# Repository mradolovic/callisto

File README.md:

# callisto
Official repository of the Visnjan Observatory e-Callisto station

Members of the Visnjan Callisto group:<br>
<br>
Marko Radolović<br>
Matej Marković<br>
Danko Marušić<br>
Korado Korlević<br>

[e-callisto.org](https://e-callisto.org/)

We owe a big thank you for helping, in this or that way, to the following:

Christian Monstein, Istituto ricerche solari Aldo e Cele Daccò<br>
Alessandro Marassi, Osservatiorio Astronomico di Trieste<br>
Mario Cifrek, Faculty of Electrical Engineering and Computing Zagreb<br>
Silvio Hrabar, Faculty of Electrical Engineering and Computing Zagreb<br>
Darin Nožina, Faculty of Electrical Engineering and Computing Zagreb<br>
Adam Alićajić, 9A4QV<br>

The CALLISTO spectrometer is a programmable heterodyne receiver designed 2006 in the framework of IHY2007 and ISWI by Christian Monstein (PI) as member of the former Radio Astronomy Group (RAG) at ETH Zurich, Switzerland. CALLISTO is an artificial word, composed as 'Compound Astronomical Low frequency Low cost Instrument for Spectroscopy and Transportable Observatory'. The main applications are observation of solar radio bursts for astronomical science, education, outreach and citizen science as well as rfi-monitoring. The instrument natively operates between 45 and 870 MHz using a modern, commercially available broadband cable-TV tuner CD1316 having a frequency resolution of 62.5 KHz. 

The data obtained from CALLISTO are FIT-files with up to 400 frequencies per sweep. The data are transferred via a RS-232 cable to a computer and saved locally. Time resolution is 0.25 sec at 200 channels per spectrum (800 spectral pixels per second). The integration time is 1 msec and the radiometric bandwidth is about 300 KHz. The overall dynamic range is larger than 50 dB. For convenient data handling several IDL-, PERL- and Python-routines were written.

Many CALLISTO instruments have already been deployed worldwide through the IHY/UNBSSI and ISWI instrument deployment program, CALLISTO is able to continuously observe the solar radio spectrum for 24h per day through all the year. All CALLISTO spectrometers together form the e-Callisto network. CALLISTO in addition is dedicated to perform radio-monitoring within its frequency range with 13'200 channels per spectrum. The frequency range can be expanded to any range by switching-in a heterodyne up- or a down-converter. Data from individual instruments are automatically uploaded by FTP to the central server at FHNW. Data which are not locked to UTC (either from the past or from the future) generate an error report.

Instrument deployment including education and training of observers was financially supported by SNF, SSAA, NASA, Institute for Astronomy and ETH Global, formerly known as North-South Center of ETH Zurich and a few private sponsors.

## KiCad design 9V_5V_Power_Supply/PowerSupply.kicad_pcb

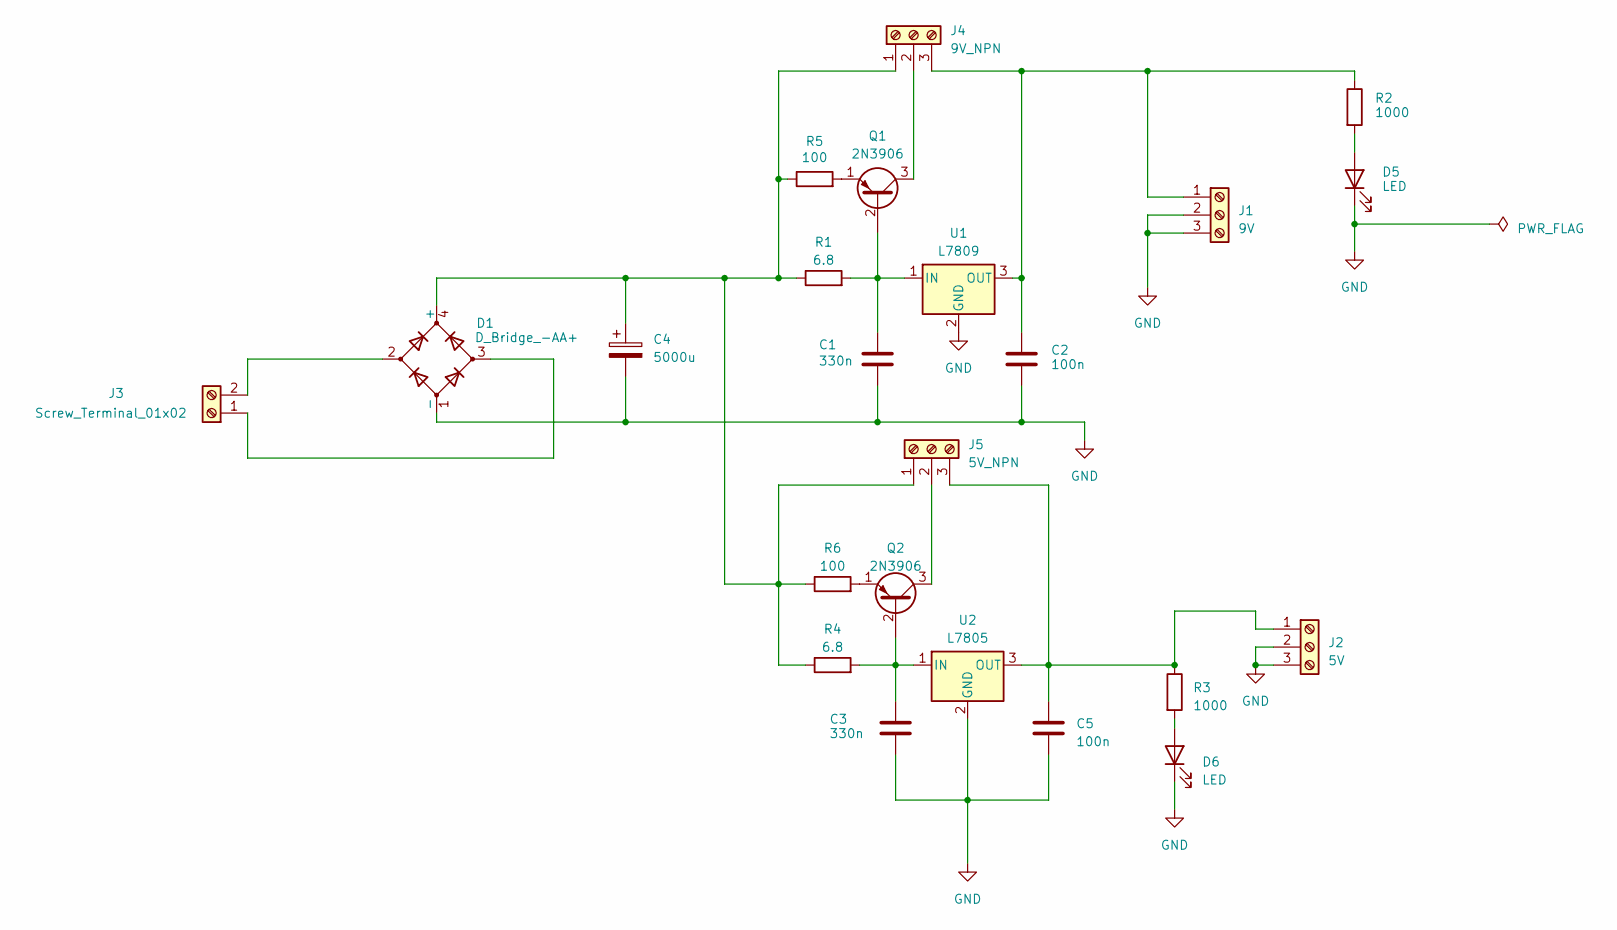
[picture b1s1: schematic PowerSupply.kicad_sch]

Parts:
C1, C3: 330n; C_Disc_D5.0mm_W2.5mm_P5.00mm
C2, C5: 100n; C_Disc_D5.0mm_W2.5mm_P5.00mm
C4: 5000u; CP_Radial_D10.0mm_P5.00mm
D1: D_Bridge_-AA+; PBL405
D5, D6: LED; LED_D3.0mm
J1: 9V; TerminalBlock_bornier-3_P5.08mm
J2: 5V; TerminalBlock_bornier-3_P5.08mm
J3: Screw_Terminal_01x02; TerminalBlock_bornier-2_P5.08mm
J4: 9V_NPN; TerminalBlock_bornier-3_P5.08mm
J5: 5V_NPN; TerminalBlock_bornier-3_P5.08mm
Q1, Q2: 2N3906; TO-92_Inline_Wide
R1, R4: 6.8; R_Axial_DIN0516_L15.5mm_D5.0mm_P20.32mm_Horizontal
R2, R3: 1000; R_0805_2012Metric_Pad1.20x1.40mm_HandSolder
R5, R6: 100; R_Axial_DIN0207_L6.3mm_D2.5mm_P10.16mm_Horizontal
U1: L7809
U2: L7805; 7805

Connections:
GND: C1.2, C2.2, C3.2, C4.2, C5.2, D1.1 (-), D5.1 (K), D6.1 (K), J1.2, J1.3, J2.2, J2.3, U1.2 (GND), U2.2 (GND)
unnamed: C4.1, D1.4 (+), J4.1, J5.1, R1.1, R4.1, R5.1, R6.1
unnamed: D5.2 (A), R2.2
unnamed: D6.2 (A), R3.2
unnamed: C2.1, J1.1, J4.3, R2.1, U1.3 (OUT)
unnamed: C5.1, J2.1, J5.3, R3.1, U2.3 (OUT)
unnamed: D1.3, J3.1
unnamed: D1.2, J3.2
unnamed: J4.2, Q1.3 (C)
unnamed: J5.2, Q2.3 (C)
unnamed: C1.1, Q1.2 (B), R1.2, U1.1 (IN)
unnamed: Q1.1 (E), R5.2
unnamed: C3.1, Q2.2 (B), R4.2, U2.1 (IN)
unnamed: Q2.1 (E), R6.2

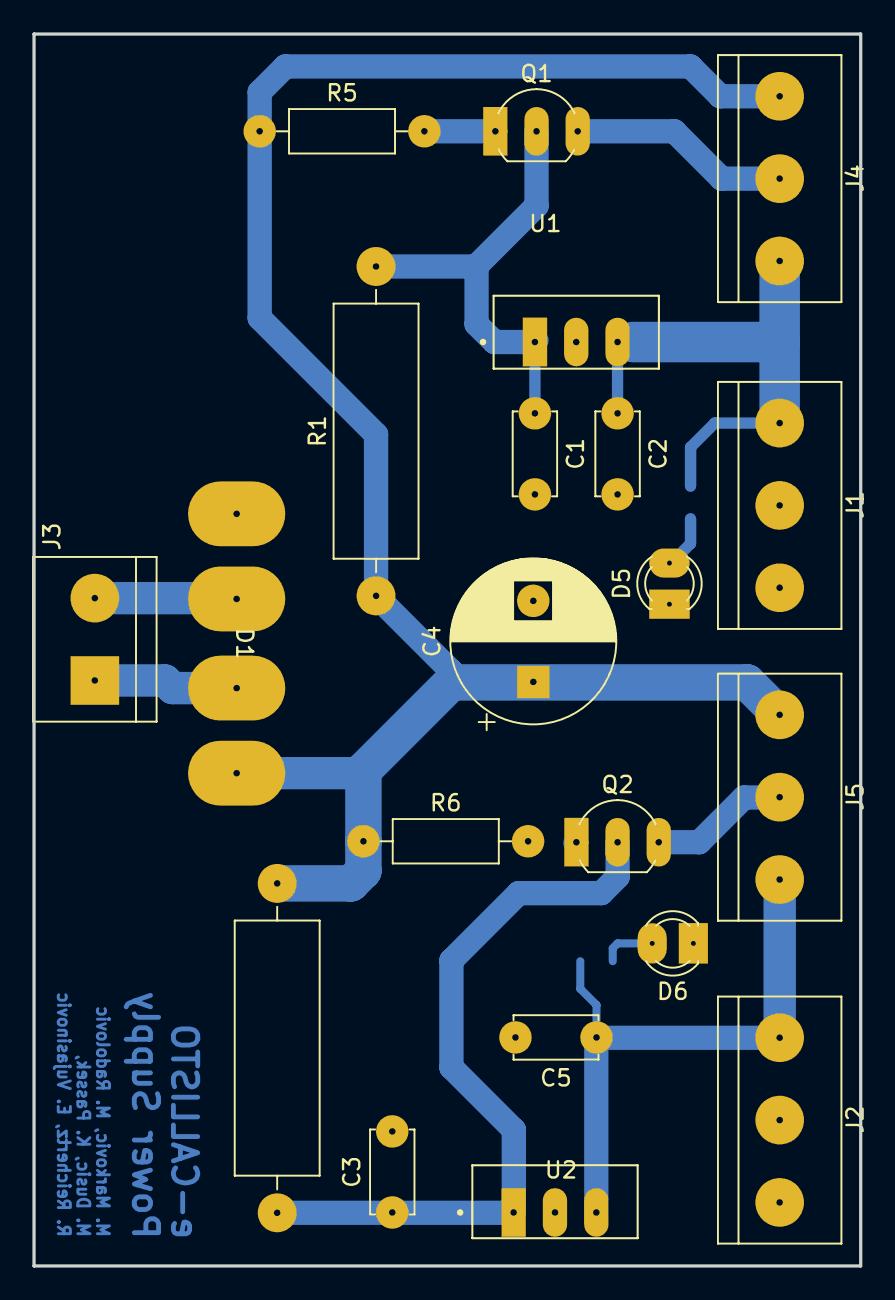
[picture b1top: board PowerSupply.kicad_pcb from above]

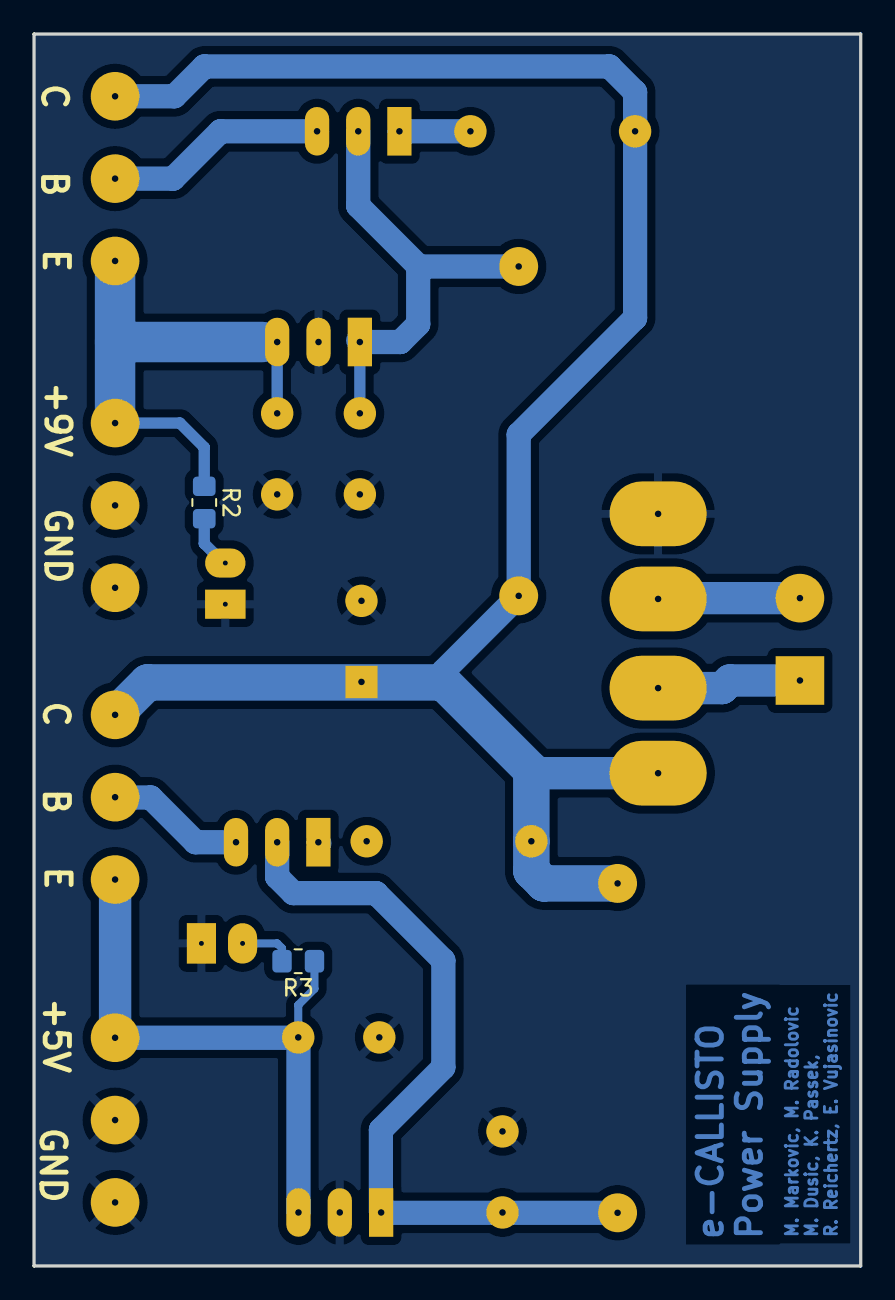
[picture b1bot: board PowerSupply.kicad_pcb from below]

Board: 2 copper layers, 51.0 x 76.0 mm, 23 parts (2 on the bottom side), 14 nets.

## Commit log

2024-08-20 Added folder for power supply
2024-08-20 Added the first version of the power supply
2024-11-18 Add files for low pass filter
2024-11-18 Add photos of LPF PCB
2024-11-18 Add files for 12V switching PS
2024-11-20 Finish schematic, finish Sch and Pcb Lib files
2024-11-20 Add files for FM notch filter
2024-11-20 Modify schematic symbol for LM2679-12
2024-11-20 Correct schematic, fix missing footprint for LM2679
2024-11-21 Change schematic to multi-layer, add footprints for INA219 and LD1117
2024-11-21 Repaired Pi Sensor Board schematic error
2024-11-21 Add ports to Pi Sensor Board
2024-11-21 Add part number for 100mOhm resistor
2024-11-23 Add 10 ohm and 0.1uF for INA219 filter
2024-11-25 Worked on layout
2024-11-26 test
2024-11-26 Change directory name to Callisto Control Board
2024-11-28 Move INA219 to bottom side
2024-11-28 Add BME280 and terminal blocks
2024-11-28 Add TMC2209 footprint and work on layout
2024-12-01 Change six 2pin to one 12pin for INA, put 0R for UART
2024-12-04 Add silkscreen and 0R for UART
2024-12-11 Add Callisto Control Board gerber and repair SXLP soldermask
2024-12-18 Export schematic into PDF
2024-12-24 Replace wrong footprint J3, move 3V3 LDO to accomodate new J3
2024-12-24 Remove unnecessary folders
2025-01-05 Add errata to Callisto control board project
2025-01-05 Reorganise Callisto Git repo
2025-01-05 Reorganisation, add software folder
2025-01-09 New version of heaterControl.py
2025-01-09 Added heaterControl new version
2025-01-09 bla bla
2025-01-11 Written new heater control code
2025-02-22 Add notes from meeting with Christian
2025-07-05 Add PCB outline, mounting holes and VDC pads
2025-09-24 Add dev branch, backup Matej's code to dev
2025-09-24 add control testing code add .gitignore
2025-09-24 Properly name the goddamn variables, thank youuu
2025-11-16 worked on xtal oscillator, just need to add filter footprint and finish the layout
2025-12-30 remove unecessary folders from altium hardware folders
2025-12-30 remove unecessary files froma ltium folders
